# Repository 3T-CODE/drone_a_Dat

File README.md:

# drone_a_Dat

## Schematic Diagram

## Top Level Schematic

### MCU

### HBridge

### Power 

## PCB

## Battery use for project 

## JLCPCB Gerber view

## Note 
For details schematic please download and view in PDF .

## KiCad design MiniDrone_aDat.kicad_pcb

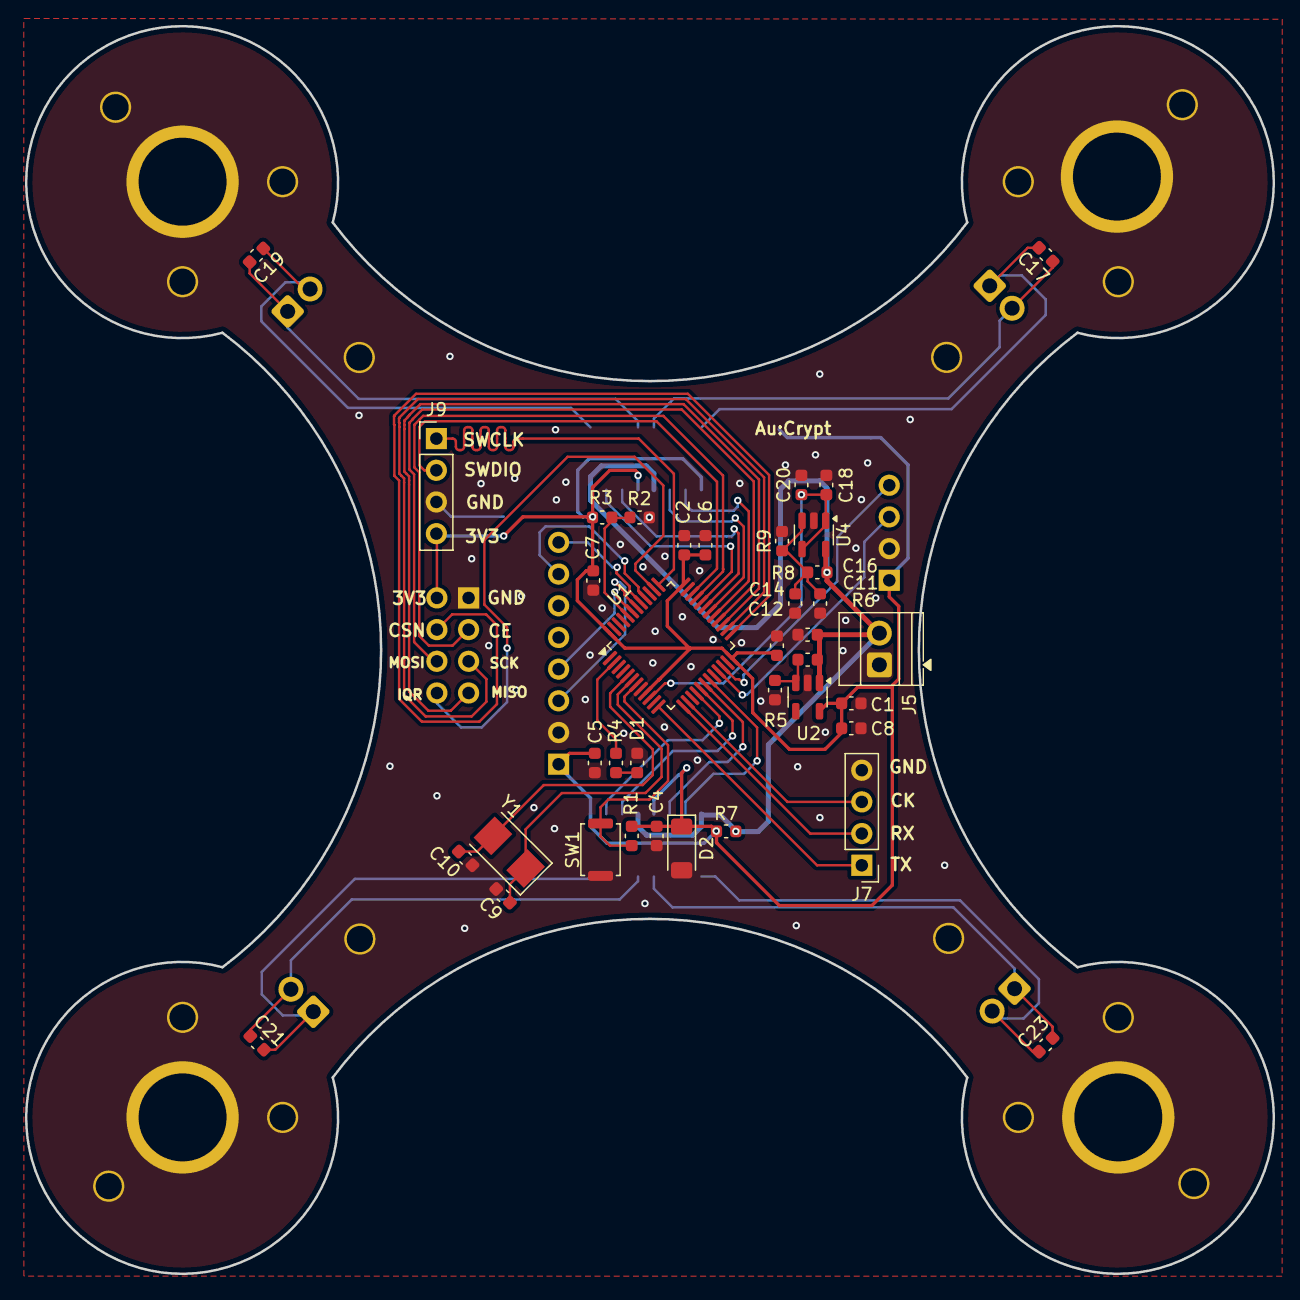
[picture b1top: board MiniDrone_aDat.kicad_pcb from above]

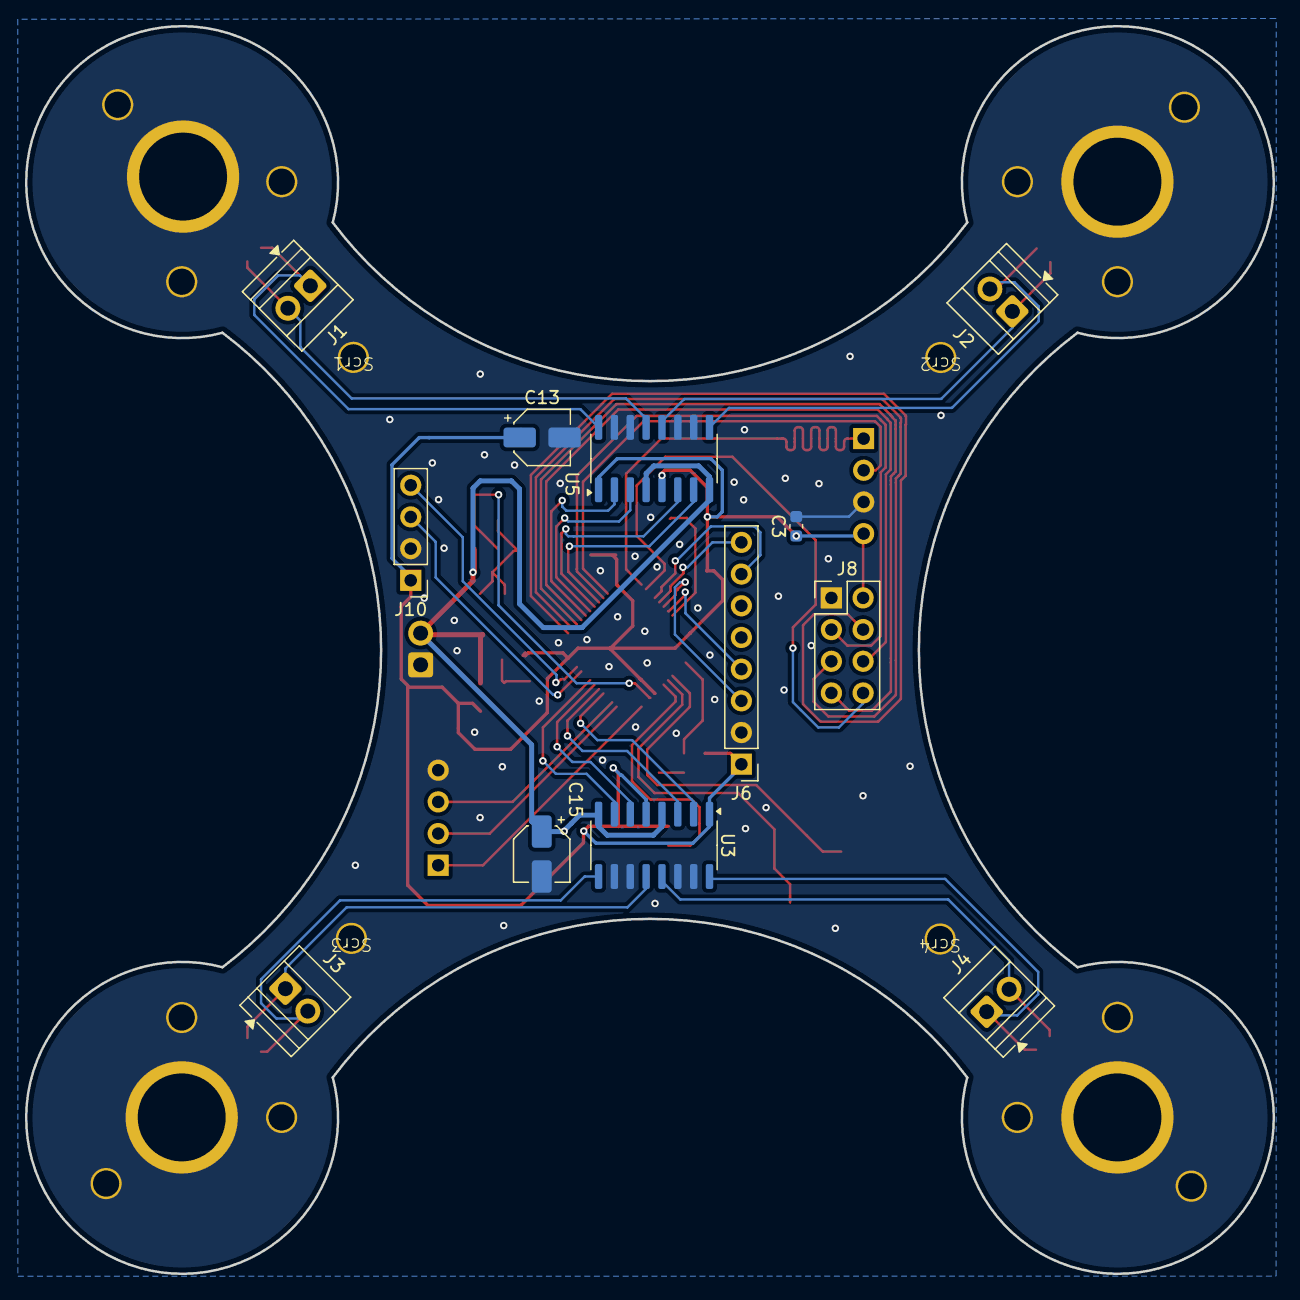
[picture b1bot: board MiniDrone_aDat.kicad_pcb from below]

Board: 2 copper layers, 100.0 x 100.0 mm, 70 parts (16 on the bottom side), 45 nets.

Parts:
C1: 10uF; C_0603_1608Metric
C2, C3, C4, C5, C6, C14, C17, C18, C19, C21, C23: 100nF; C_0603_1608Metric
C7: 10nF; C_0603_1608Metric
C8, C11, C12, C16, C20: 1uF; C_0603_1608Metric
C9, C10: 15pF; C_0603_1608Metric
C13, C15: 4.7uF; CP_Elec_4x5.4
D1: LED; C_0603_1608Metric
D2: ZMMxx; D_MiniMELF
J1, J2, J3, J4, J5: Screw_Terminal_01x02; TerminalBlock_Xinya_XY308-2.54-2P_1x02_P2.54mm_Horizontal
J6: Conn_01x08; PinHeader_1x08_P2.54mm_Vertical
J7, J9, J10: Conn_01x04; PinHeader_1x04_P2.54mm_Vertical
J8: Conn_02x04_Counter_Clockwise; PinHeader_2x04_P2.54mm_Vertical
Mt1, Mt2, Mt3, Mt4: 720DCMotor
R1, R3, R5: 10kOhm; C_0603_1608Metric
R2, R6: 0Ohm; C_0603_1608Metric
R4: 1kOhm; C_0603_1608Metric
R7: 220Ohm; C_0603_1608Metric
R8: 5.6KOhm; C_0603_1608Metric
R9: 20kOhm; C_0603_1608Metric
SW1: SW_Push; SW_Push_SPST_NO_Alps_SKRK
Scr1, Scr2, Scr3, Scr4, Scr5, Scr6, Scr7, Scr8, Scr9, Scr10, Scr11, Scr12, Scr13, Scr14, Scr15, Scr16: ScrewM2
U1: STM32F103C8Tx; LQFP-48_7x7mm_P0.5mm
U2: ADP7142AUJZ-3.3; TSOT-23-5
U3, U5: MX1508; SOP-16_3.9x9.9mm_P1.27mm
U4: MCP601-xOT; SOT-23-5
Y1: 5032 2P; Crystal_SMD_5032-2Pin_5.0x3.2mm

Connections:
+3V3: C1.1, C2.1, C3.1, C4.1, C5.1, C6.1, C7.1, C8.1, C12.1, C13.1, D2.1 (K), J6.1, J8.2, J9.4, J10.1, R1.1, R3.2, R7.1, U1.9 (VDDA), U1.24 (VDD), U1.36 (VDD), U1.48 (VDD), U2.5 (VOUT), U3.1 (VCC), U3.5 (VCC), U5.1 (VCC), U5.5 (VCC)
/TopLevelDesign/HBridge/H1_INA1: U1.29 (PA8), U5.2 (INA1)
/TopLevelDesign/HBridge/H1_INA2: U1.31 (PA10), U5.6 (INA2)
/TopLevelDesign/HBridge/H1_INB1: U1.30 (PA9), U5.3 (INB1)
/TopLevelDesign/HBridge/H1_INB2: U1.32 (PA11), U5.7 (INB2)
/TopLevelDesign/HBridge/H1_OUTA1: C17.2, J1.1, U5.16 (OUTA1)
/TopLevelDesign/HBridge/H1_OUTA2: C19.2, J2.1, U5.12 (OUTA2)
/TopLevelDesign/HBridge/H1_OUTB1: C17.1, J1.2, U5.13 (OUTB1)
/TopLevelDesign/HBridge/H1_OUTB2: C19.1, J2.2, U5.9 (OUTB2)
/TopLevelDesign/HBridge/H2_INA1: U1.16 (PA6), U3.2 (INA1)
/TopLevelDesign/HBridge/H2_INA2: U1.18 (PB0), U3.6 (INA2)
/TopLevelDesign/HBridge/H2_INB1: U1.17 (PA7), U3.3 (INB1)
/TopLevelDesign/HBridge/H2_INB2: U1.19 (PB1), U3.7 (INB2)
/TopLevelDesign/HBridge/H2_OUTA1: C21.2, J4.1, U3.16 (OUTA1)
/TopLevelDesign/HBridge/H2_OUTA2: C23.2, J3.1, U3.12 (OUTA2)
/TopLevelDesign/HBridge/H2_OUTB1: C21.1, J4.2, U3.13 (OUTB1)
/TopLevelDesign/HBridge/H2_OUTB2: C23.1, J3.2, U3.9 (OUTB2)
/TopLevelDesign/MCU/PA0: C18.1, C20.1, U1.10 (PA0), U4.1, U4.4 (-)
/TopLevelDesign/PA2: J7.1, U1.12 (PA2)
/TopLevelDesign/PA3: J7.2, U1.13 (PA3)
/TopLevelDesign/PA4: J7.3, U1.14 (PA4)
/TopLevelDesign/PA12: J8.3, U1.33 (PA12)
/TopLevelDesign/PA15: J8.8, U1.38 (PA15)
/TopLevelDesign/PB4: J6.7, U1.40 (PB4)
/TopLevelDesign/PB5: J6.8, U1.41 (PB5)
/TopLevelDesign/PB6: J6.3, U1.42 (PB6)
/TopLevelDesign/PB7: J6.4, U1.43 (PB7)
/TopLevelDesign/PB10: J10.3, U1.21 (PB10)
/TopLevelDesign/PB11: J10.4, U1.22 (PB11)
/TopLevelDesign/PB12: J8.4, U1.25 (PB12)
/TopLevelDesign/PB13: J8.5, U1.26 (PB13)
/TopLevelDesign/PB14: J8.7, U1.27 (PB14)
/TopLevelDesign/PB15: J8.6, U1.28 (PB15)
/TopLevelDesign/SWCLK: J9.1, U1.37 (PA14)
/TopLevelDesign/SWDIO: J9.2, U1.34 (PA13)
GND: C1.2, C2.2, C3.2, C4.2, C5.2, C6.2, C7.2, C8.2, C9.2, C10.2, C11.2, C12.2, C13.2, C14.2, C15.2, C16.2, C18.2, C20.2, D1.1 (K), D2.2 (A), J5.1, J6.2, J7.4, J8.1, J9.3, J10.2, Mt1.GND, Mt2.GND, Mt3.GND, Mt4.GND, R2.1, R5.2, R9.2, SW1.1, Scr1.GND, Scr2.GND, Scr3.GND, Scr4.GND, Scr5.GND, Scr6.GND, Scr7.GND, Scr8.GND, Scr9.GND, Scr10.GND, Scr11.GND, Scr12.GND, Scr13.GND, Scr14.GND, Scr15.GND, Scr16.GND, U1.8 (VSSA), U1.23 (VSS), U1.35 (VSS), U1.47 (VSS), U2.2 (GND), U3.10 (GND), U3.11 (GND), U3.14 (GND), U3.15 (GND), U4.2 (V-), U5.10 (GND), U5.11 (GND), U5.14 (GND), U5.15 (GND)
unnamed: D1.2 (A), R4.2
unnamed: R2.2, R3.1, U1.44 (BOOT0)
unnamed: R1.2, SW1.2, U1.7 (NRST)
unnamed: R4.1, U1.2 (PC13)
unnamed: C10.1, U1.5 (PD0), Y1.2
unnamed: C9.1, U1.6 (PD1), Y1.1
unnamed: R5.1, R6.1, U2.3 (EN)
unnamed: C14.1, C16.1, R8.1, R9.1, U4.3 (+)
Vin: C11.1, C15.1, J5.2, R6.2, R7.2, R8.2, U2.1 (VIN), U3.4 (VDD), U3.8 (VDD), U4.5 (V+), U5.4 (VDD), U5.8 (VDD)

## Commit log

2025-06-20 20/6/2025
2025-07-02 2/7/2025
2025-07-04 4/7/2025
2025-07-05 5/7/2025
2025-07-06 6/7/2025
